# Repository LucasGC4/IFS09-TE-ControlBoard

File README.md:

# IFS09-TE-ControlBoard

Hardware design and KiCad schematics/PCB layout for the **Control Board (ECU Node)** of the **IFS09**, developed for the **ISC Formula Student Racing Team** (Season 2026/2027). This is a first onboarding project for the Electronics & Control subsystem — the board's mission is to become the vehicle's ECU node, reading dual CAN buses and analog/digital sensors from the AMPSEAL car harness.

.pdf>)

---

## Getting started

1. Create a GitHub account if you don't have one yet.
2. Download and install [GitHub Desktop](https://desktop.github.com/) (beginner) or [Git CLI](https://git-scm.com/book/en/v2/Getting-Started-Installing-Git) (advanced).
3. Install [KiCad 10](https://www.kicad.org/download/) (or latest stable) and, if needed, link the team's shared library [`IFS-KicadLib`](https://github.com/isc-fs/IFS-KicadLib) for team-standard symbols and footprints.
4. Clone this repository to your machine:
   - **SSH:** `git@github.com:LucasGC4/IFS09-TE-ControlBoard.git`
   - **HTTPS:** `https://github.com/LucasGC4/IFS09-TE-ControlBoard.git`

---

## How we work with this repository

Following ISC's standard branching rules:

* **`main`** holds only validated releases. Never commit directly to it.
* Active design work happens on feature branches (`feat/<name>`, `fix/<name>`) created from `main`, merged back through a reviewed Pull Request.

```bash
git checkout main
git pull origin main
git checkout -b feat/your-feature-name
# ... work and commit ...
git commit -m "hw: add CAN2 split termination network"
git push origin feat/your-feature-name
```

Before opening a PR: verify **0 KiCad ERC/DRC errors** and export an updated `Schematics-X.X.pdf`.

---

## 1. Project Overview & System Purpose

The **IFS09 Control Board** is an automotive-grade microcontroller node connected to the car's 24V Low Voltage battery and both CAN communication buses, intended to read sensors and drive vehicle actuators.

```
+------------------------------------------------------------------------+
|                    IFS09 CAR WIRING HARNESS                            |
|   +24V LV Battery -- CAN1 -- CAN2 -- 2x Digital In -- 2x Analog In     |
+---------------------------------+----------------------------------------+
                                  |
                     AMPSEAL 14-Pin (J1, 1-776087-1)
                                  |
+---------------------------------v----------------------------------------+
|                       IFS09 CONTROL BOARD (ECU NODE)                    |
|                                                                          |
|  +24V --> [TSR 1-2450 Buck, U1] --> 5V --> [LM2936-3.3 LDO, U2] --> 3V3 |
|                                                                          |
|  CAN1 <--> [TCAN330, U3] --\                                           |
|                              >--- SPI/GPIO ---> [STM32H7A3IGTxQ, U4]    |
|  CAN2 <--> [TCAN330, U5] --/            (LQFP-176, 16 MHz osc. Y1)      |
|                                                                          |
|  Status LEDs (24V/5V/3.3V/Heartbeat) · SWD (J4) · UART+I2C (J2) · SPI (J3) |
+--------------------------------------------------------------------------+
```

### Key Highlights
* **Processing:** STM32H7A3IGTxQ (LQFP-176) with a 16 MHz active oscillator (`Y1`, XUX53) with isolated ground plane.
* **Power chain:** 24V → 5V via `U1` (TSR 1-2450 DC/DC module, fused with `F1` 2A), then 5V → 3.3V via `U2` (LM2936-3.3, TO-92).
* **CAN interfaces:** Two independent `TCAN330` transceivers (`U3` for CAN1, `U5` for CAN2), each with a 120 Ω bus termination resistor (`R5`, `R6`) and 100 nF decoupling.
* **Vehicle connector:** Single AMPSEAL-style 23-position header (`J1`, part `1-776087-1`) carries +24V, GND, CAN1, CAN2, and a 3V3 line to/from the harness.
* **Decoupling:** A bank of ~40 ceramic capacitors (mostly 100 nF, plus bulk caps) placed across the MCU's `VDD`/`VDDA` pins.
* **Diagnostics:** Four status LEDs (24V, 5V, 3.3V, Heartbeat) and four test points (`TP1`–`TP4`).
* **Debug/expansion headers:** `J4` (SWD), `J2` (UART + I²C), `J3` (SPI) — see pinout below.
* **Mechanical:** Four mounting holes (`H1`–`H4`), rounded-corner outline, 2-layer PCB (`F.Cu`/`B.Cu`).

---

## 2. Hardware Architecture & Schematic Design

The schematic export is available as [`Schematics.pdf`](Schematics.pdf), organized into labeled functional blocks matching the sections below.

### 2.1 Schematic Subsystem Breakdown

#### 1. Power Converters (24V → 5V → 3.3V)
* `F1` (2A fuse) protects the +24V input line.
* `U1` — **TSR 1-2450** DC/DC converter module steps 24V down to 5V, with `C3`/`C4` (10 µF) at input/output.
* `U2` — **LM2936-3.3 (TO-92)** LDO regulates 5V down to a clean 3.3V rail, with `C1`/`C2` (10 nF/100 nF) decoupling.

#### 2. Microcontroller (`U4` — STM32H7A3IGTxQ, LQFP-176)
* Clocked by a 16 MHz active oscillator (`Y1`, XUX53) placed in its own labeled section for ground isolation.
* Reset circuit: push button `SW1` with debounce capacitor `C11` (100 nF) and pull-up `R9` (10 kΩ) on `NRST`.
* `VCAP` pins filtered with `C6`/`C8` (2.2 µF).
* A large bank of decoupling capacitors (`C12`–`C55` range, mostly 100 nF, plus one 4.7 µF bulk cap) covers the MCU's power pins.

#### 3. Dual CAN Transceivers (`U3`, `U5` — TCAN330)
* `U3` interfaces `CAN1_TX`/`CAN1_RX` from the MCU to `CAN1_H`/`CAN1_L`, terminated by `R5` (120 Ω).
* `U5` interfaces `CAN2_TX`/`CAN2_RX` to `CAN2_H`/`CAN2_L`, terminated by `R6` (120 Ω).
* Each transceiver has its own 100 nF decoupling capacitor (`C9`, `C10`).

#### 4. Status LEDs & Test Points
* `D1`/`R1` (10 kΩ) — 24V rail indicator.
* `D2`/`R2` (1 kΩ) — 5V rail indicator.
* `D3`/`R3` (680 Ω) — 3.3V rail indicator.
* `D4`/`R4` (1 kΩ) — Heartbeat LED driven by the MCU.
* `TP1`–`TP4` — test points for the four rails/signals shown above.

---

## 3. PCB Layout & Physical Implementation

<p align="center">
  
  &nbsp;&nbsp;&nbsp;&nbsp;
  
</p>

* 2-layer board (`F.Cu` / `B.Cu`), rounded-corner outline, four M3-class mounting holes (`H1`–`H4`) at the corners.
* `J1` (AMPSEAL) is placed along the top edge for direct harness mating; the MCU (`U4`) sits centrally with debug/expansion headers (`J2`, `J3`, `J4`) broken out along the bottom edge.

---

## 4. Pinout & Hardware Interfacing

### 4.1 Vehicle Connector — `J1` (`1-776087-1`, AMPSEAL-style, 23-position)

| Pin(s) | Signal | Notes |
| :--- | :--- | :--- |
| 1, 2 | `+24V` | Battery input (tied together) |
| 5 | `CAN1_L` | CAN Bus 1 |
| 6 | `CAN1_H` | CAN Bus 1 |
| 7 | `CAN2_L` | CAN Bus 2 |
| 8 | `CAN2_H` | CAN Bus 2 |
| 9 | `3V3` | 3.3V line to/from harness |
| 10, 11 | `GND` | Ground |
| 13 | `5V` | 5V output |
| 14 | `GND` | Ground |
| 3, 4, 15–23 | *NC* | Not connected in this revision |

### 4.2 Debug & Expansion Headers

| Header | Type | Pin 1 | Pin 2 | Pin 3 | Pin 4 | Pin 5 |
| :--- | :--- | :--- | :--- | :--- | :--- | :--- |
| `J4` | SWD (5-pin) | `3V3` | `SWDIO` | `SWCLK` | `NRST` | `GND` |
| `J2` | UART + I²C (4-pin) | `UART_TX` | `UART_RX` | `I2C_SDA` | `I2C_SCL` | — |
| `J3` | SPI (4-pin) | `SPI_NSS` | `SPI_SCK` | `SPI_MISO` | `SPI_MOSI` | — |

> I²C lines (`I2C_SDA`/`I2C_SCL`) are pulled up to 3V3 via `R7`/`R8` (4.7 kΩ each).

---

## 5. Repository Structure

```
IFS09-TE-ControlBoard/
├── images/                                  # PCB layout/render exports
│   ├── pcb_layout_2d.png                    # 2D PCB Layout Routing View
│   └── pcb_render_3d.png                    # 3D PCB Render Model
├── IFS09-ControlBoard/                      # KiCad Project Files (KiCad 10.x)
│   ├── IFS09-ControlBoard.kicad_pro         # Project Configuration
│   ├── IFS09-ControlBoard.kicad_sch         # Schematic Sheet
│   └── IFS09-ControlBoard.kicad_pcb         # PCB Layout & Netlist
├── WO_TE-IFS09-ControlBoard (1).pdf         # Work Order / onboarding brief (Rev 1.1)
├── Schematics.pdf                           # Exported schematic sheet
└── README.md                                # This file
```

> **Not yet in the repository:** a Design Report (`DR_TE-IFS09-ControlBoard.pdf`) and a `SW/` firmware folder — both are still pending, per the Work Order's submission checklist.

---

## 6. Formal Design Documents

| Document | File Link | Description | Status |
| :--- | :--- | :--- | :--- |
| **Work Order** | [📄 WO_TE-IFS09-ControlBoard (1).pdf](<WO_TE-IFS09-ControlBoard (1).pdf>) | Onboarding roadmap, requirements, and pinout brief (Rev 1.1). | **Released** |
| **Schematics** | [📄 Schematics.pdf](Schematics.pdf) | Exported schematic sheet. | Current |
| **Design Report** | *(not yet created)* | Component justifications, BOM, and post-assembly test results. | **Pending** |

---

## 7. Acceptance Testing Checklist (Post-Assembly Bench QA)

As defined in the Work Order, once the board is assembled:

1. **Passive short-circuit check:** resistance from each supply test point to `GND` must read **> 10 kΩ** before power-up.
2. **Power-up & regulation:** with a 24V bench supply (current-limited to 200 mA), verify `TP2` (5V) = 5.0 V ± 0.2 V and `TP3` (3.3V) = 3.3 V ± 0.05 V, and that all power LEDs light up.
3. **SWD detection & MCU flash:** connect ST-Link to `J4` and flash test firmware to blink the Heartbeat LED (`D4`).
4. **Dual CAN loopback:** connect `CAN1`/`CAN2` to a USB-CAN adapter (PCAN/CANable) and verify send/receive at 500 kbit/s with zero dropped frames.
5. **Bus probing:** check `SPI` (`J3`) and `UART`/`I2C` (`J2`) lines with an oscilloscope for clean signals.

---

## 8. Author & Credits

* **Subsystem:** Electronics & Control (CE)
* **Author:** Lucas García Cucala
* **Mentorship & Review:** Carlota Treviño, Félix González, Inés Pacheco, Andrés Sánchez de Ágreda
* **Team:** [ISC Formula Student Racing Team](https://www.comillas.edu/) — Universidad Pontificia Comillas (ICAI)
* **Season:** 2026 / 2027

---

*ISC Racing Team — IFS09 Electronics & Control Subsystem*

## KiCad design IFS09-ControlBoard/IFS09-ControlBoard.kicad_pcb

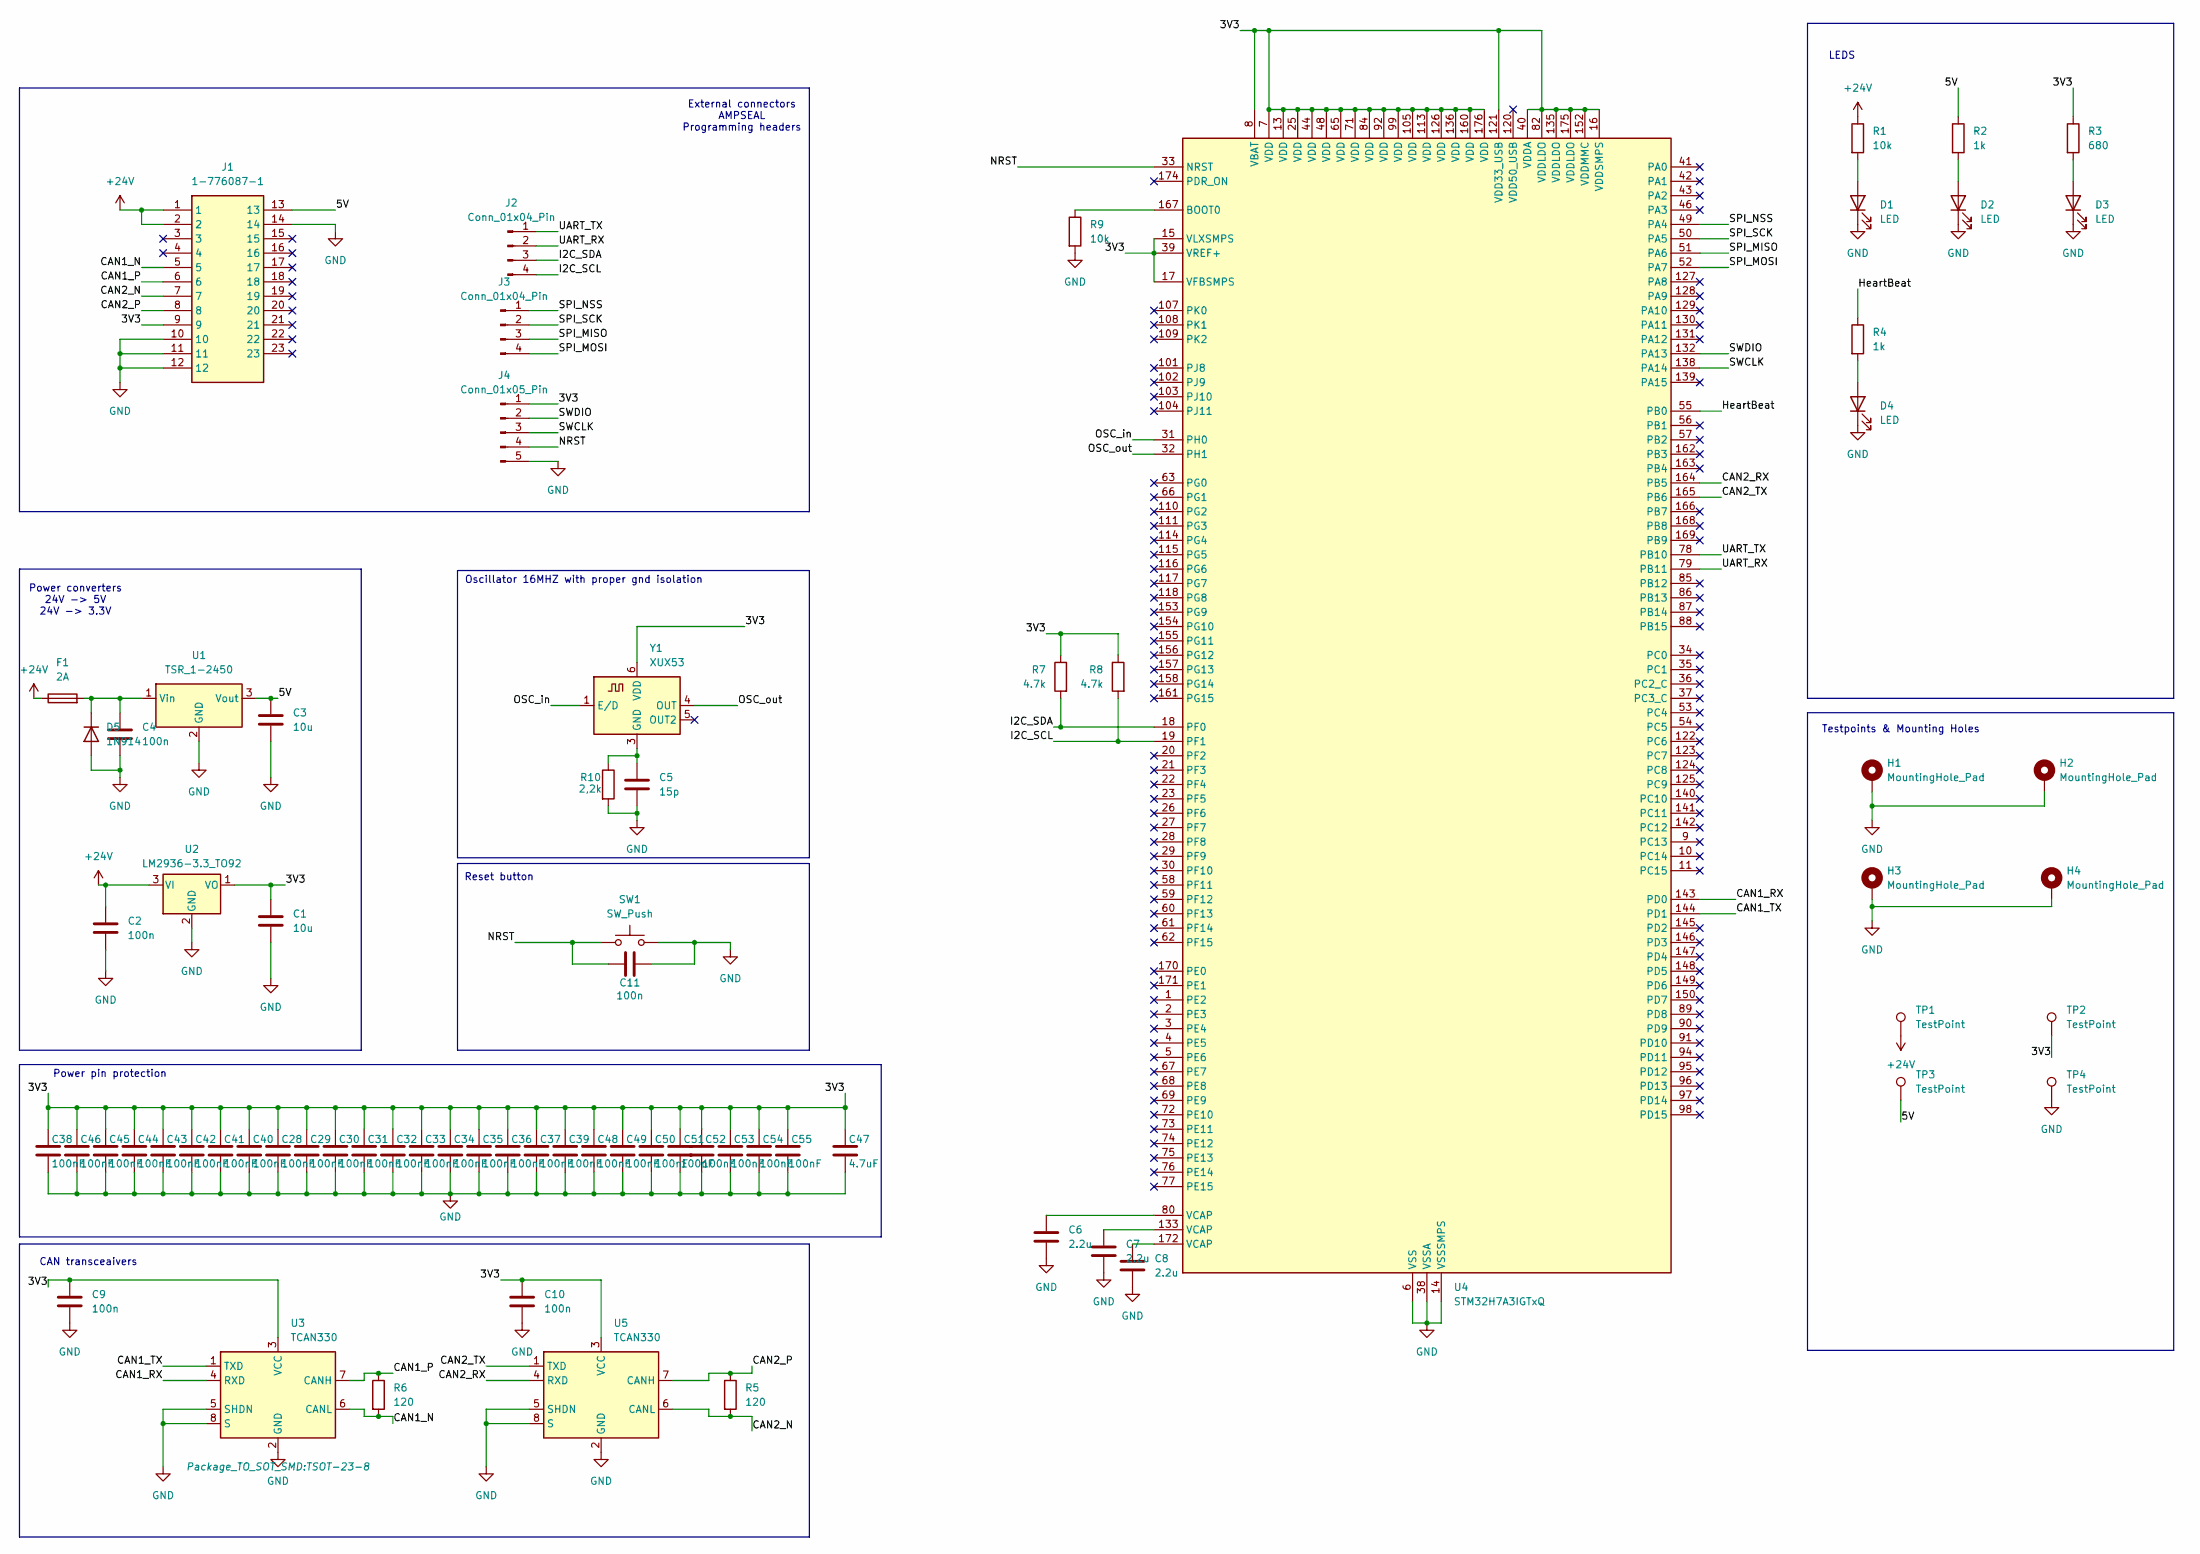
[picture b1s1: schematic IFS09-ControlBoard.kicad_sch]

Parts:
C1, C3: 10u; C_0805_2012Metric
C2, C4, C9, C10, C11: 100n; C_0805_2012Metric
C5: 15p; C_0805_2012Metric_Pad1.18x1.45mm_HandSolder
C6, C7, C8: 2.2u; C_0805_2012Metric_Pad1.18x1.45mm_HandSolder
C28, C29, C30, C31, C32, C33, C34, C35, C36, C37, C38, C39, C40, C41, C42, C43, C44, C45, C46, C48, C49, C50, C51, C52, C53, C54, C55: 100nF; C_0603_1608Metric_Pad1.08x0.95mm_HandSolder
C47: 4.7uF; C_0603_1608Metric_Pad1.08x0.95mm_HandSolder
D1, D2, D3, D4: LED; LED_0805_2012Metric_Pad1.15x1.40mm_HandSolder
D5: 1N914; D_DO-35_SOD27_P7.62mm_Horizontal
F1: 2A; Fuse_0805_2012Metric
H1, H2, H3, H4: MountingHole_Pad; MountingHole_3.2mm_M3_Pad
J1: 1-776087-1; 17760871; Mouser Part Number 571-1-776087-1
J2, J3: Conn_01x04_Pin; PinHeader_1x04_P2.54mm_Vertical
J4: Conn_01x05_Pin; PinHeader_1x05_P2.54mm_Vertical
R1, R9: 10k; R_0805_2012Metric_Pad1.20x1.40mm_HandSolder
R2, R4: 1k; R_0805_2012Metric_Pad1.20x1.40mm_HandSolder
R3: 680; R_0805_2012Metric_Pad1.20x1.40mm_HandSolder
R5, R6: 120; R_0805_2012Metric
R7, R8: 4.7k; R_0805_2012Metric_Pad1.20x1.40mm_HandSolder
R10: 2,2k; R_0805_2012Metric
SW1: SW_Push; Panasonic_EVQPUK_EVQPUB
TP1, TP2, TP3, TP4: TestPoint; TestPoint_Pad_D2.0mm
U1: TSR_1-2450; Converter_DCDC_TRACO_TSR-1_THT
U2: LM2936-3.3_TO92; TO-92_Inline
U3, U5: TCAN330; TSOT-23-8
U4: STM32H7A3IGTxQ; LQFP-176_24x24mm_P0.5mm
Y1: XUX53; Oscillator_SMD_IDT_JS6-6_5.0x3.2mm_P1.27mm

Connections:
+24V: C2.1, F1.1, J1.1, J1.2, R1.1, TP1.1 (1_1), U2.3 (VI)
/3V3: C1.1, C9.1, C10.1, C28.1, C29.1, C30.1, C31.1, C32.1, C33.1, C34.1, C35.1, C36.1, C37.1, C38.1, C39.1, C40.1, C41.1, C42.1, C43.1, C44.1, C45.1, C46.1, C47.1, C48.1, C49.1, C50.1, C51.1, C52.1, C53.1, C54.1, C55.1, J1.9, J4.1, R3.1, R7.1, R8.1, TP2.1 (1_1), U2.1 (VO), U3.3 (VCC), U4.7 (VDD), U4.8 (VBAT), U4.13 (VDD), U4.15 (VLXSMPS), U4.16 (VDDSMPS), U4.17 (VFBSMPS), U4.25 (VDD), U4.39 (VREF+), U4.40 (VDDA), U4.44 (VDD), U4.48 (VDD), U4.65 (VDD), U4.71 (VDD), U4.82 (VDDLDO), U4.84 (VDD), U4.92 (VDD), U4.99 (VDD), U4.105 (VDD), U4.113 (VDD), U4.121 (VDD33_USB), U4.126 (VDD), U4.135 (VDDLDO), U4.136 (VDD), U4.152 (VDDMMC), U4.160 (VDD), U4.175 (VDDLDO), U4.176 (VDD), U5.3 (VCC), Y1.6 (VDD)
/5V: C3.1, J1.13, R2.1, TP3.1 (1_1), U1.3 (Vout)
/CAN1_N: J1.5, R6.2, U3.6 (CANL)
/CAN1_P: J1.6, R6.1, U3.7 (CANH)
/CAN1_RX: U3.4 (RXD), U4.143 (PD0)
/CAN1_TX: U3.1 (TXD), U4.144 (PD1)
/CAN2_N: J1.7, R5.2, U5.6 (CANL)
/CAN2_P: J1.8, R5.1, U5.7 (CANH)
/CAN2_RX: U4.164 (PB5), U5.4 (RXD)
/CAN2_TX: U4.165 (PB6), U5.1 (TXD)
/HeartBeat: R4.1, U4.55 (PB0)
/I2C_SCL: J2.4, R8.2, U4.19 (PF1)
/I2C_SDA: J2.3, R7.2, U4.18 (PF0)
/NRST: C11.2, J4.4, SW1.1, U4.33 (NRST)
/OSC_in: U4.31 (PH0), Y1.1 (E/D)
/OSC_out: U4.32 (PH1), Y1.4 (OUT)
/SPI_MISO: J3.3, U4.51 (PA6)
/SPI_MOSI: J3.4, U4.52 (PA7)
/SPI_NSS: J3.1, U4.49 (PA4)
/SPI_SCK: J3.2, U4.50 (PA5)
/SWCLK: J4.3, U4.138 (PA14)
/SWDIO: J4.2, U4.132 (PA13)
/UART_RX: J2.2, U4.79 (PB11)
/UART_TX: J2.1, U4.78 (PB10)
GND: C1.2, C2.2, C3.2, C4.2, C5.2, C6.2, C7.2, C8.2, C9.2, C10.2, C11.1, C28.2, C29.2, C30.2, C31.2, C32.2, C33.2, C34.2, C35.2, C36.2, C37.2, C38.2, C39.2, C40.2, C41.2, C42.2, C43.2, C44.2, C45.2, C46.2, C47.2, C48.2, C49.2, C50.2, C51.2, C52.2, C53.2, C54.2, C55.2, D1.1 (K), D2.1 (K), D3.1 (K), D4.1 (K), D5.2 (A), H1.1 (1_1), H2.1 (1_1), H3.1 (1_1), H4.1 (1_1), J1.10, J1.11, J1.12, J1.14, J4.5, R9.2, R10.2, SW1.2, TP4.1 (1_1), U1.2 (GND), U2.2 (GND), U3.2 (GND), U3.5 (SHDN), U3.8 (S), U4.6 (VSS), U4.12 (VSS), U4.14 (VSSSMPS), U4.24 (VSS), U4.38 (VSSA), U4.45 (VSS), U4.47 (VSS), U4.64 (VSS), U4.70 (VSS), U4.81 (VSS), U4.83 (VSS), U4.93 (VSS), U4.100 (VSS), U4.106 (VSS), U4.112 (VSS), U4.119 (VSS), U4.134 (VSS), U4.137 (VSS), U4.151 (VSS), U4.159 (VSS), U4.173 (VSS), U5.2 (GND), U5.5 (SHDN), U5.8 (S)
unnamed: C6.1, U4.80 (VCAP)
unnamed: C7.1, U4.133 (VCAP)
unnamed: C8.1, U4.172 (VCAP)
unnamed: D1.2 (A), R1.2
unnamed: D2.2 (A), R2.2
unnamed: D3.2 (A), R3.2
unnamed: D4.2 (A), R4.2
unnamed: C4.1, D5.1 (K), F1.2, U1.1 (Vin)
unnamed: R9.1, U4.167 (BOOT0)
unnamed: C5.1, R10.1, Y1.3 (GND)

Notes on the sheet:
Power converters 24V -> 5V 24V -> 3.3V
Power pin protection
Testpoints & Mounting Holes
Oscillator 16MHZ with proper gnd isolation
Reset button
CAN transceaivers
External connectors AMPSEAL Programming headers
LEDS

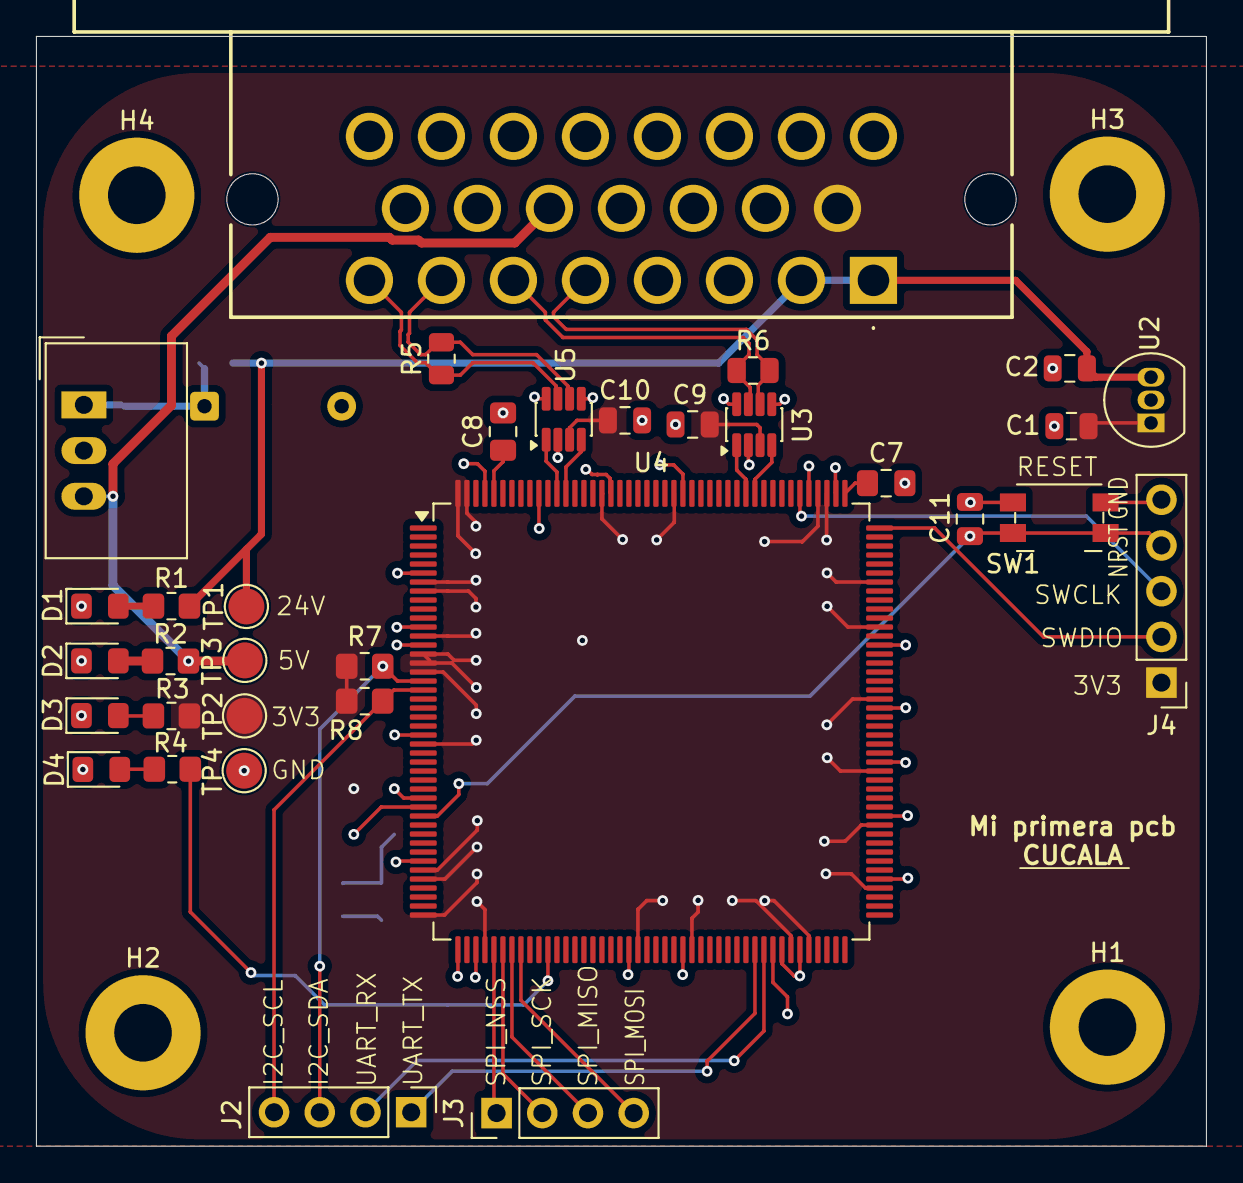
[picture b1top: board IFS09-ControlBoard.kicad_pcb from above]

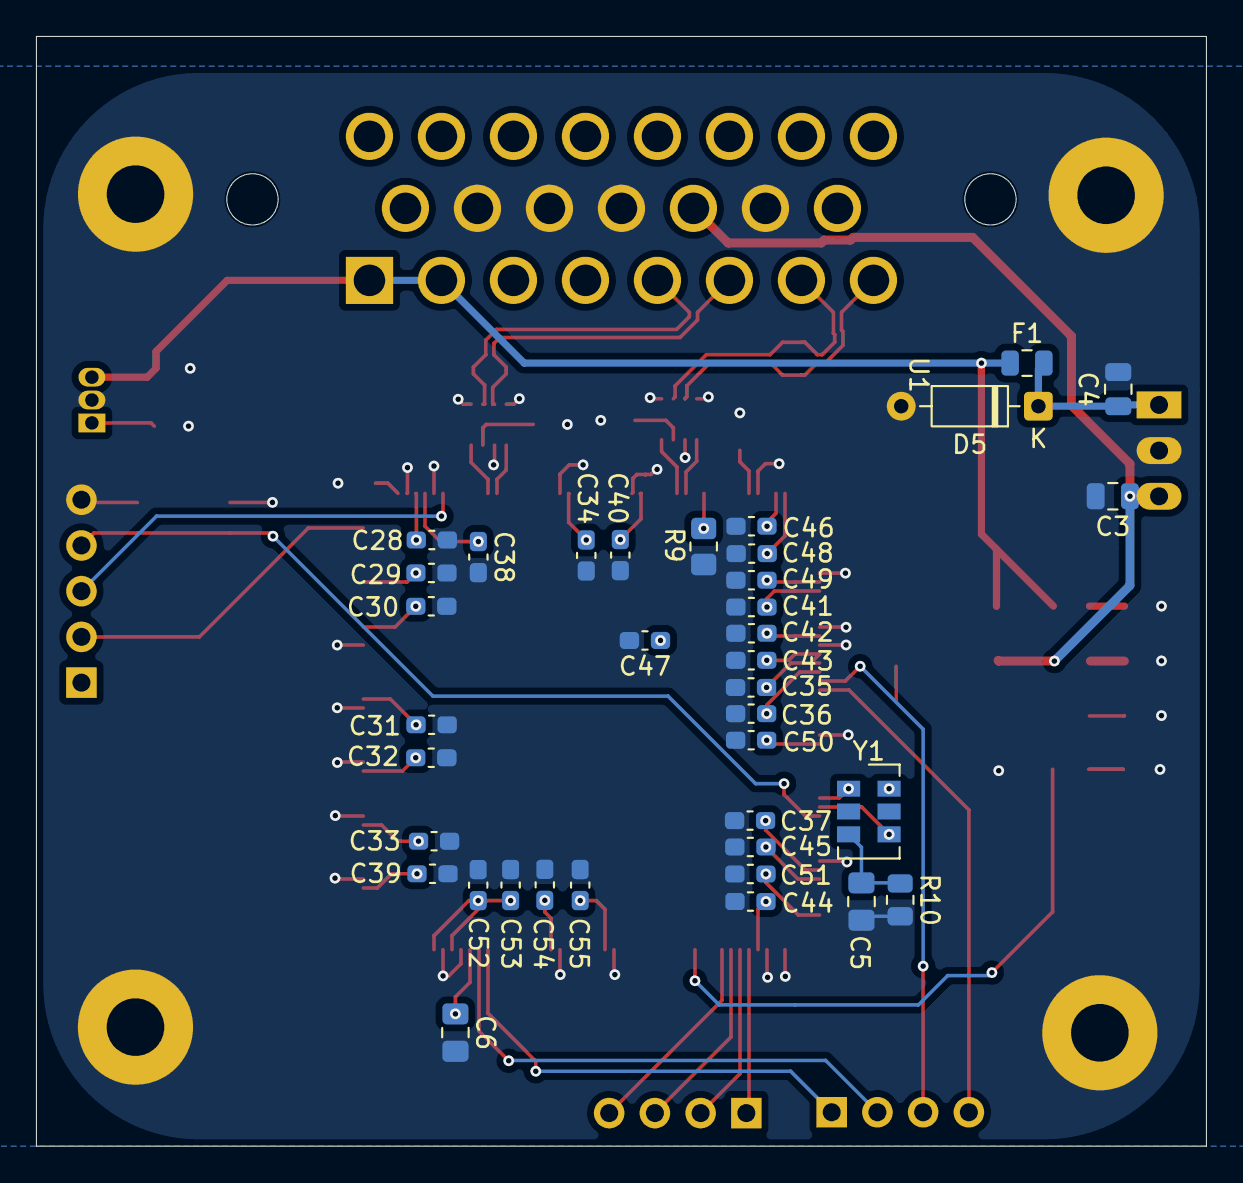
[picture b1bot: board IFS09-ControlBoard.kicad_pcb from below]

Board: 2 copper layers, 65.0 x 61.6 mm, 74 parts (37 on the bottom side), 36 nets.
